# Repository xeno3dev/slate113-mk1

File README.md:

# Slate113 Mk1

## Overview

Slate113 Mk1 is a Beefy Phone-Like Cyberdeck, powered by the [ArmSOM CM5](https://www.armsom.org/product-page/cm5?variantId=052f14c0-9009-4c4c-8e45-79380a8dca78), and meant to be a more capable and feature-rich alternative to the Flipper One.

## Inspired By
[Pi Flux by Carbon Computers](https://carboncomputers.us/products/pi-flux) and the [Flipper One by Flipper Devices](https://blog.flipper.net/flipper-one-we-need-your-help/)

## Features
- DP Alt Mode
- ESP32 Co-Processor
- NFC via PN7160
- RFID via EM3095
- Sub-GHz via CC1101
- BadUSB
- Wi-Fi 6/6E and BLE 5.2
- 6 SMAs (Interchangable between GPS, WIFI, Sub-GHz, BLE, and LTE)
- SlateConnect (Custom Board-Edge Connector System)
- GNSS w/ IMU
- Cellular Modem (via M.2 B-Key Slot)
- Stereo Bottom Firing Speakers (w/ Amps)
- MEMS Microphone
- Side Mounted Customizable Adressable RGB LED Strip

## Sheets¹

### Main Board

Sheet BOM [here](./Manufacturing%20Files/BOMs/Per%20Sheet/slate113-mk1_main_board.csv)

---

### IO

Sheet BOM [here](./Manufacturing%20Files/BOMs/Per%20Sheet/slate113-mk1_io.csv)

---

### Power

Sheet BOM [here](./Manufacturing%20Files/BOMs/Per%20Sheet/slate113-mk1_power.csv)

---

### M.2

Sheet BOM [here](./Manufacturing%20Files/BOMs/Per%20Sheet/slate113-mk1_m.2.csv)

---

### Radio

Sheet BOM [here](./Manufacturing%20Files/BOMs/Per%20Sheet/slate113-mk1_radio.csv)

---

### Antenna Bracket

Sheet BOM [here](./Manufacturing%20Files/BOMs/Per%20Sheet/slate113-mk1_antennabracket.csv)

---

### SlateConnect

Sheet BOM [here](./Manufacturing%20Files/BOMs/Per%20Sheet/slate113-mk1_slateconnect.csv)

---

### LED Bar

Sheet BOM [here](./Manufacturing%20Files/BOMs/Per%20Sheet/slate113-mk1_ledbar.csv)

---

### PCB(s)²

Total BOM [here](./Manufacturing%20Files/BOMs/slate113-mk1.csv)

---

### Total Price Breakdown
---
| Item | Price | Link |
| --- | --- | --- |
| Main Board | USD$14.31 | [BOM](./Manufacturing%20Files/BOMs/Per%20Sheet/slate113-mk1_main_board.csv) |
| IO Board + Flex | USD$85.59 | [BOM](./Manufacturing%20Files/BOMs/Per%20Sheet/slate113-mk1_io.csv) |
| Power Board + Flex | USD$15.81 | [BOM](./Manufacturing%20Files/BOMs/Per%20Sheet/slate113-mk1_power.csv) |
| M.2 Board + Flex | USD$7.23 | [BOM](./Manufacturing%20Files/BOMs/Per%20Sheet/slate113-mk1_m.2.csv) |
| Radio Board + Flex | USD$77.90 | [BOM](./Manufacturing%20Files/BOMs/Per%20Sheet/slate113-mk1_radio.csv) |
| Antenna Bracket | USD$15.17 | [BOM](./Manufacturing%20Files/BOMs/Per%20Sheet/slate113-mk1_antennabracket.csv) |
| SlateConnect + Flex | USD$16.31 | [BOM](./Manufacturing%20Files/BOMs/Per%20Sheet/slate113-mk1_slateconnect.csv) |
| LED Bar Flex | USD$7.39 | [BOM](./Manufacturing%20Files/BOMs/Per%20Sheet/slate113-mk1_ledbar.csv) |
| Display | USD$55.49³ | [Alibaba Link](https://www.alibaba.com/product-detail/Industrial-5-5inch-Touch-Screen-720_1601790231031.html?spm=a2756.order-detail-ta-ta-b.0.0.fb3ef19cmzzMxB) |
| PCBs | ~USD$531⁴ | [JLCPCB](https://jlcpcb.com/) |

**Estimated Total**: US$971.53–1,286.53⁴

---

## Fineprint

¹Certain Sheets aren't included here, such as the Slate113 Sheet, as it's the root sheet, and has nothing, and the flex sheets (excluding the LED Bar Flex), as they are just two of the same connectors.

---

²Not Done at the time of writing this.

---

³Includes SHipping and DDP

---

⁴All parts haven't been finalized, including items like enclosure, battery, and others; subject to change

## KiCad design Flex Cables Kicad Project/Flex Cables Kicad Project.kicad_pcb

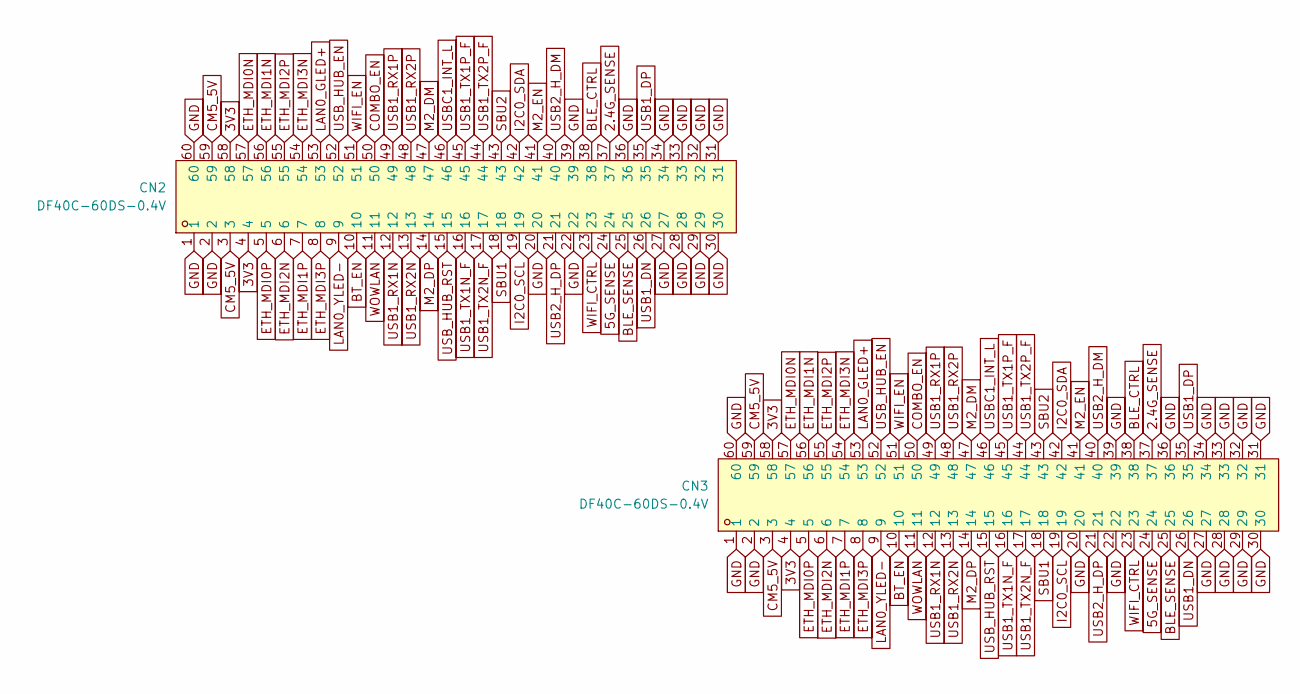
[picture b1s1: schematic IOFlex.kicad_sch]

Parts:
CN2, CN3: DF40C-60DS-0.4V; CONN-SMD_DF40C-60DS-0.4V-51; MPN DF40C-60DS-0.4V(51); LCSC Part C597938

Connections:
2.4G_SENSE: CN2.37, CN3.37
3V3: CN2.4, CN2.58, CN3.4, CN3.58; also elsewhere on the board
5G_SENSE: CN2.24, CN3.24
BLE_CTRL: CN2.38, CN3.38
BLE_SENSE: CN2.25, CN3.25
BT_EN: CN2.10, CN3.10
CM5_5V: CN2.3, CN2.59, CN3.3, CN3.59; also elsewhere on the board
COMBO_EN: CN2.50, CN3.50
ETH_MDI0N: CN2.57, CN3.57
ETH_MDI0P: CN2.5, CN3.5
ETH_MDI1N: CN2.56, CN3.56
ETH_MDI1P: CN2.7, CN3.7
ETH_MDI2N: CN2.6, CN3.6
ETH_MDI2P: CN2.55, CN3.55
ETH_MDI3N: CN2.54, CN3.54
ETH_MDI3P: CN2.8, CN3.8
GND: CN2.1, CN2.2, CN2.20, CN2.22, CN2.27, CN2.28, CN2.29, CN2.30, CN2.31, CN2.32, CN2.33, CN2.34, CN2.36, CN2.39, CN2.60, CN3.1, CN3.2, CN3.20, CN3.22, CN3.27, CN3.28, CN3.29, CN3.30, CN3.31, CN3.32, CN3.33, CN3.34, CN3.36, CN3.39, CN3.60; also elsewhere on the board
I2C0_SCL: CN2.19, CN3.19; also elsewhere on the board
I2C0_SDA: CN2.42, CN3.42; also elsewhere on the board
LAN0_GLED+: CN2.53, CN3.53
LAN0_YLED-: CN2.9, CN3.9
M2_DM: CN2.47, CN3.47; also elsewhere on the board
M2_DP: CN2.14, CN3.14; also elsewhere on the board
M2_EN: CN2.41, CN3.41
SBU1: CN2.18, CN3.18
SBU2: CN2.43, CN3.43
USB1_DN: CN2.26, CN3.26
USB1_DP: CN2.35, CN3.35
USB1_RX1N: CN2.12, CN3.12
USB1_RX1P: CN2.49, CN3.49
USB1_RX2N: CN2.13, CN3.13
USB1_RX2P: CN2.48, CN3.48
USB1_TX1N_F: CN2.16, CN3.16
USB1_TX1P_F: CN2.45, CN3.45
USB1_TX2N_F: CN2.17, CN3.17
USB1_TX2P_F: CN2.44, CN3.44
USB2_H_DM: CN2.40, CN3.40
USB2_H_DP: CN2.21, CN3.21
USBC1_INT_L: CN2.46, CN3.46
USB_HUB_EN: CN2.52, CN3.52
USB_HUB_RST: CN2.15, CN3.15
WIFI_CTRL: CN2.23, CN3.23
WIFI_EN: CN2.51, CN3.51
WOWLAN: CN2.11, CN3.11

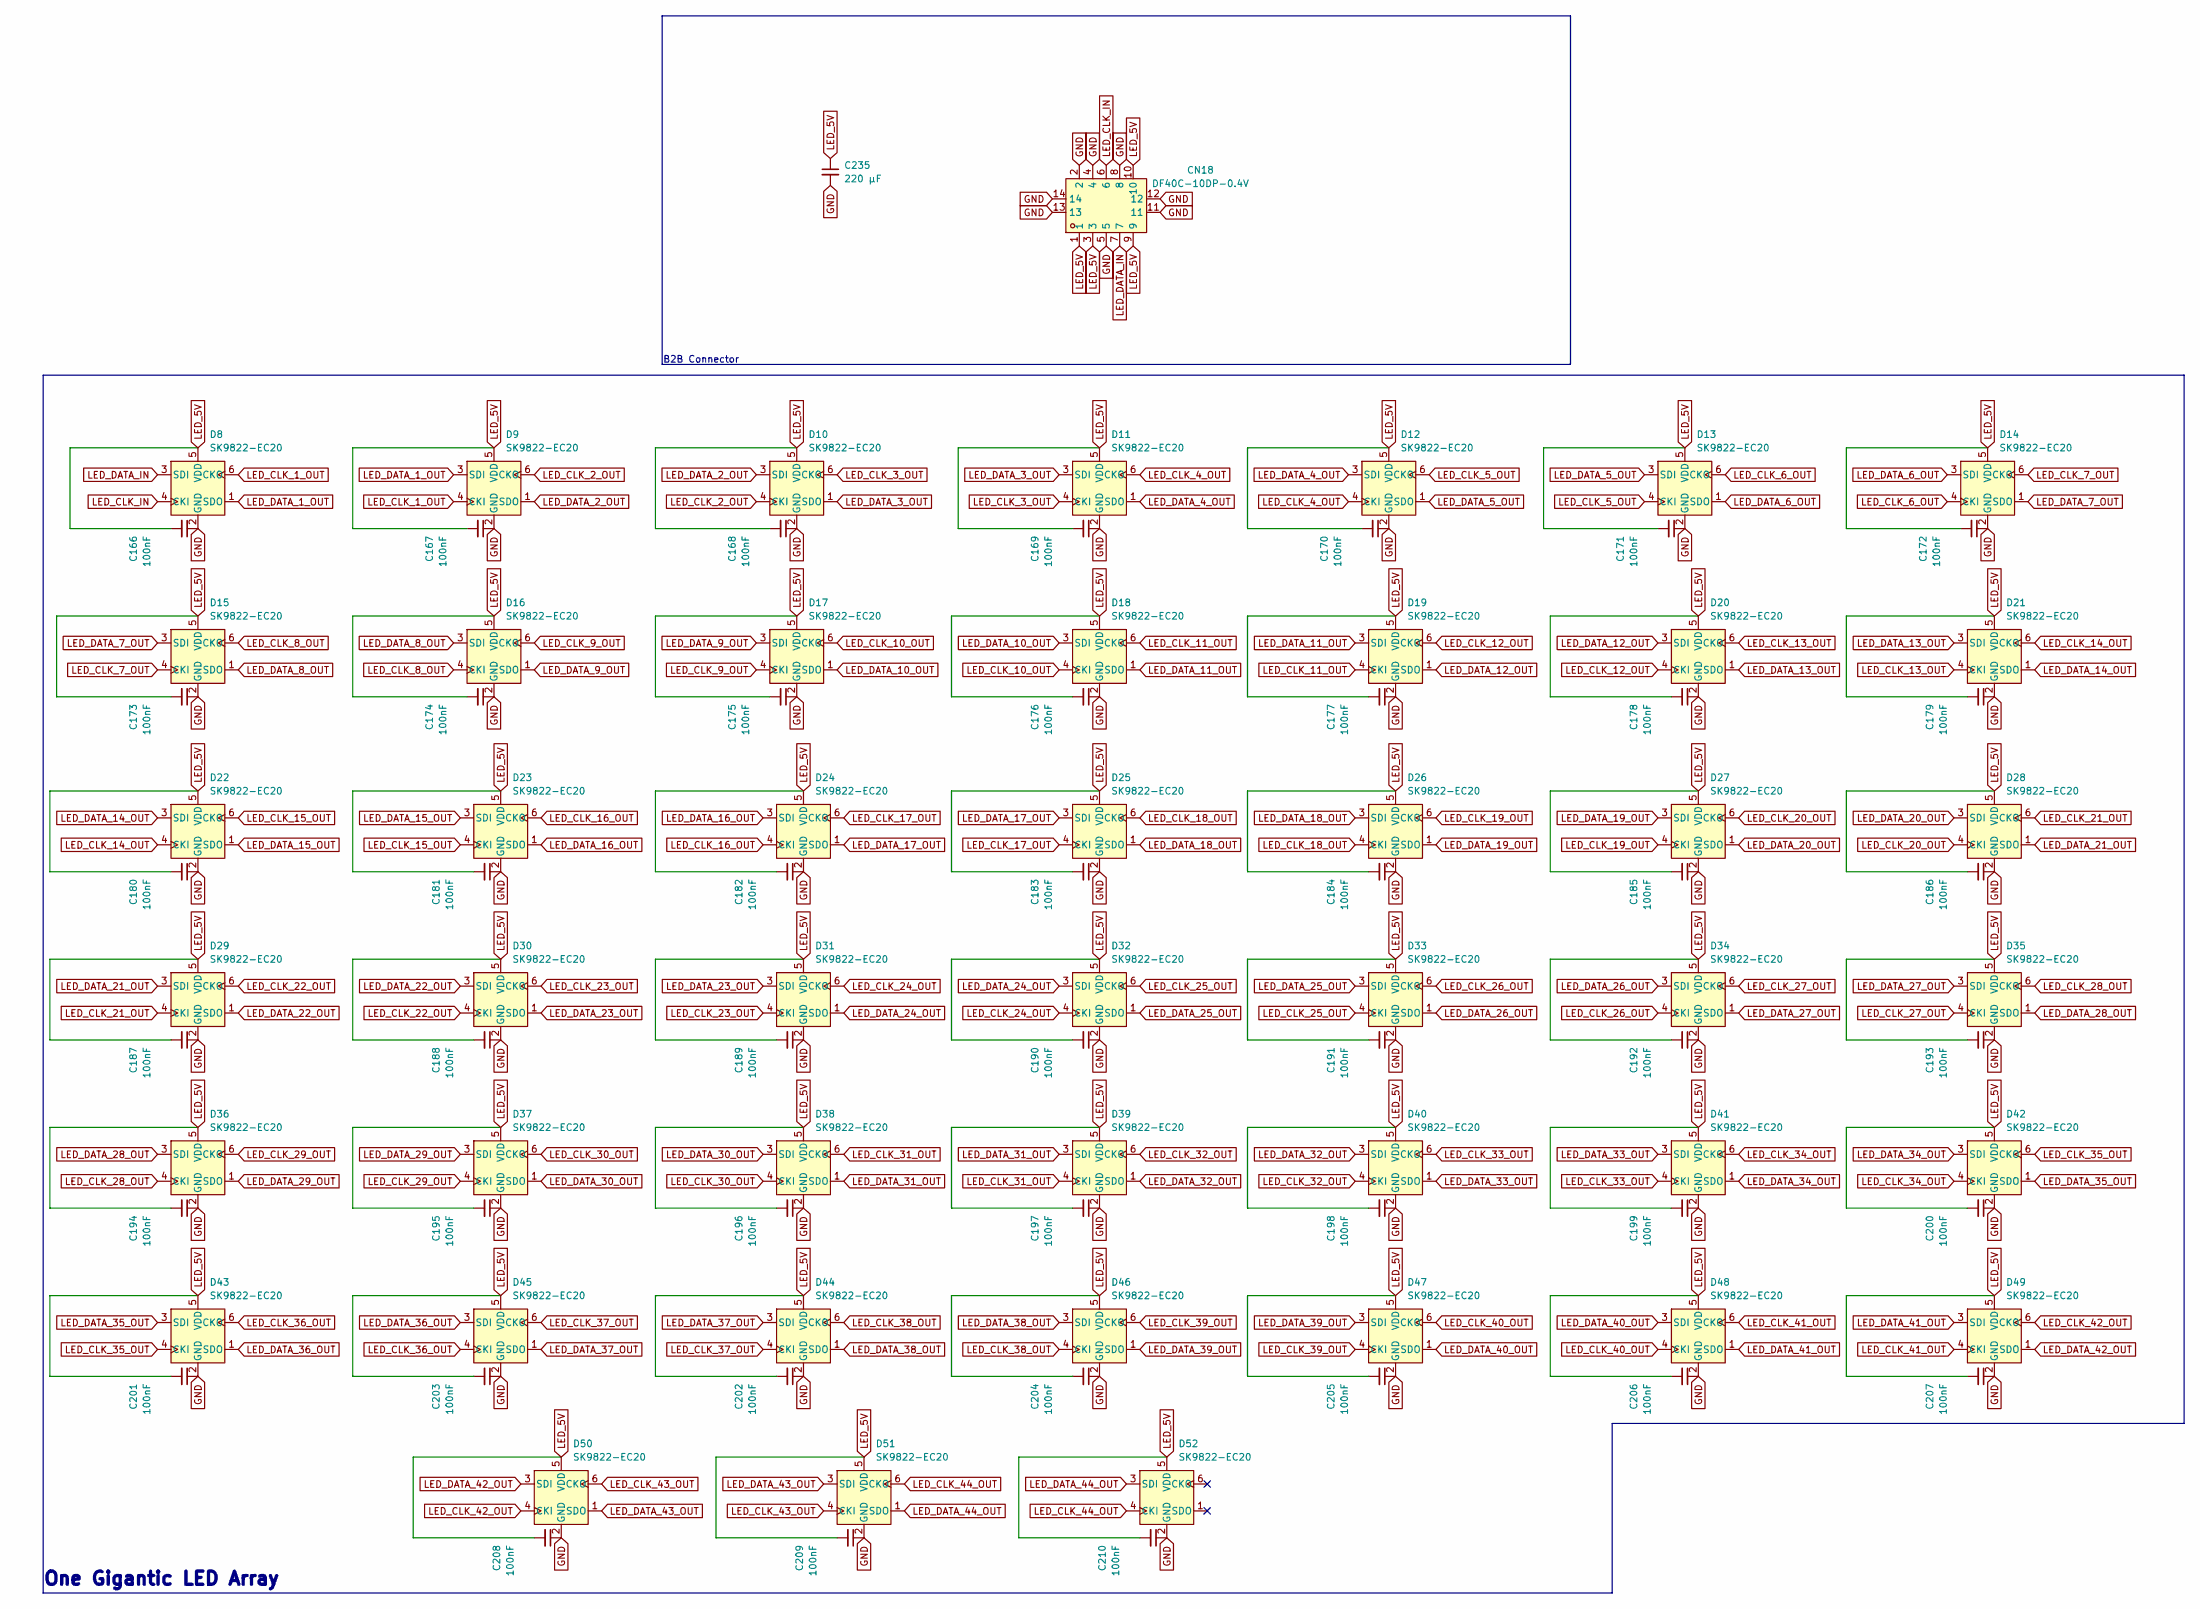
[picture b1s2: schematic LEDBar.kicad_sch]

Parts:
C166, C167, C168, C169, C170, C171, C172, C173, C174, C175, C176, C177, C178, C179, C180, C181, C182, C183, C184, C185, C186, C187, C188, C189, C190, C191, C192, C193, C194, C195, C196, C197, C198, C199, C200, C201, C202, C203, C204, C205, C206, C207, C208, C209, C210: 100nF; C_0603_1608Metric; MPN CL10B104KB8NNNC; LCSC Part C1591
C235: 220 µF; CHEMI-F61; MPN APXF6R3ARA221MF61G; DigiKey Part 565-3163-1-ND
CN18: DF40C-10DP-0.4V; CONN-SMD_10P-P0.40_DF40C-10DP-0.4V-51; MPN DF40C-10DP-0.4V(51); LCSC Part C424635
D8, D9, D10, D11, D12, D13, D14, D15, D16, D17, D18, D19, D20, D21, D22, D23, D24, D25, D26, D27, D28, D29, D30, D31, D32, D33, D34, D35, D36, D37, D38, D39, D40, D41, D42, D43, D44, D45, D46, D47, D48, D49, D50, D51, D52: SK9822-EC20; MPN SK9822-EC20; LCSC Part C2909059

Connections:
GND: C166.1, C167.1, C168.1, C169.1, C170.1, C171.1, C172.1, C173.1, C174.1, C175.1, C176.1, C177.1, C178.1, C179.1, C180.1, C181.1, C182.1, C183.1, C184.1, C185.1, C186.1, C187.1, C188.1, C189.1, C190.1, C191.1, C192.1, C193.1, C194.1, C195.1, C196.1, C197.1, C198.1, C199.1, C200.1, C201.1, C202.1, C203.1, C204.1, C205.1, C206.1, C207.1, C208.1, C209.1, C210.1, C235.2, CN18.2, CN18.4, CN18.5, CN18.8, CN18.11, CN18.12, CN18.13, CN18.14, D8.2 (GND), D9.2 (GND), D10.2 (GND), D11.2 (GND), D12.2 (GND), D13.2 (GND), D14.2 (GND), D15.2 (GND), D16.2 (GND), D17.2 (GND), D18.2 (GND), D19.2 (GND), D20.2 (GND), D21.2 (GND), D22.2 (GND), D23.2 (GND), D24.2 (GND), D25.2 (GND), D26.2 (GND), D27.2 (GND), D28.2 (GND), D29.2 (GND), D30.2 (GND), D31.2 (GND), D32.2 (GND), D33.2 (GND), D34.2 (GND), D35.2 (GND), D36.2 (GND), D37.2 (GND), D38.2 (GND), D39.2 (GND), D40.2 (GND), D41.2 (GND), D42.2 (GND), D43.2 (GND), D44.2 (GND), D45.2 (GND), D46.2 (GND), D47.2 (GND), D48.2 (GND), D49.2 (GND), D50.2 (GND), D51.2 (GND), D52.2 (GND); also elsewhere on the board
LED_5V: C166.2, C167.2, C168.2, C169.2, C170.2, C171.2, C172.2, C173.2, C174.2, C175.2, C176.2, C177.2, C178.2, C179.2, C180.2, C181.2, C182.2, C183.2, C184.2, C185.2, C186.2, C187.2, C188.2, C189.2, C190.2, C191.2, C192.2, C193.2, C194.2, C195.2, C196.2, C197.2, C198.2, C199.2, C200.2, C201.2, C202.2, C203.2, C204.2, C205.2, C206.2, C207.2, C208.2, C209.2, C210.2, C235.1, CN18.1, CN18.3, CN18.9, CN18.10, D8.5 (VDD), D9.5 (VDD), D10.5 (VDD), D11.5 (VDD), D12.5 (VDD), D13.5 (VDD), D14.5 (VDD), D15.5 (VDD), D16.5 (VDD), D17.5 (VDD), D18.5 (VDD), D19.5 (VDD), D20.5 (VDD), D21.5 (VDD), D22.5 (VDD), D23.5 (VDD), D24.5 (VDD), D25.5 (VDD), D26.5 (VDD), D27.5 (VDD), D28.5 (VDD), D29.5 (VDD), D30.5 (VDD), D31.5 (VDD), D32.5 (VDD), D33.5 (VDD), D34.5 (VDD), D35.5 (VDD), D36.5 (VDD), D37.5 (VDD), D38.5 (VDD), D39.5 (VDD), D40.5 (VDD), D41.5 (VDD), D42.5 (VDD), D43.5 (VDD), D44.5 (VDD), D45.5 (VDD), D46.5 (VDD), D47.5 (VDD), D48.5 (VDD), D49.5 (VDD), D50.5 (VDD), D51.5 (VDD), D52.5 (VDD)
LED_CLK_1_OUT: D8.6 (CKO), D9.4 (CKI)
LED_CLK_2_OUT: D9.6 (CKO), D10.4 (CKI)
LED_CLK_3_OUT: D10.6 (CKO), D11.4 (CKI)
LED_CLK_4_OUT: D11.6 (CKO), D12.4 (CKI)
LED_CLK_5_OUT: D12.6 (CKO), D13.4 (CKI)
LED_CLK_6_OUT: D13.6 (CKO), D14.4 (CKI)
LED_CLK_7_OUT: D14.6 (CKO), D15.4 (CKI)
LED_CLK_8_OUT: D15.6 (CKO), D16.4 (CKI)
LED_CLK_9_OUT: D16.6 (CKO), D17.4 (CKI)
LED_CLK_10_OUT: D17.6 (CKO), D18.4 (CKI)
LED_CLK_11_OUT: D18.6 (CKO), D19.4 (CKI)
LED_CLK_12_OUT: D19.6 (CKO), D20.4 (CKI)
LED_CLK_13_OUT: D20.6 (CKO), D21.4 (CKI)
LED_CLK_14_OUT: D21.6 (CKO), D22.4 (CKI)
LED_CLK_15_OUT: D22.6 (CKO), D23.4 (CKI)
LED_CLK_16_OUT: D23.6 (CKO), D24.4 (CKI)
LED_CLK_17_OUT: D24.6 (CKO), D25.4 (CKI)
LED_CLK_18_OUT: D25.6 (CKO), D26.4 (CKI)
LED_CLK_19_OUT: D26.6 (CKO), D27.4 (CKI)
LED_CLK_20_OUT: D27.6 (CKO), D28.4 (CKI)
LED_CLK_21_OUT: D28.6 (CKO), D29.4 (CKI)
LED_CLK_22_OUT: D29.6 (CKO), D30.4 (CKI)
LED_CLK_23_OUT: D30.6 (CKO), D31.4 (CKI)
LED_CLK_24_OUT: D31.6 (CKO), D32.4 (CKI)
LED_CLK_25_OUT: D32.6 (CKO), D33.4 (CKI)
LED_CLK_26_OUT: D33.6 (CKO), D34.4 (CKI)
LED_CLK_27_OUT: D34.6 (CKO), D35.4 (CKI)
LED_CLK_28_OUT: D35.6 (CKO), D36.4 (CKI)
LED_CLK_29_OUT: D36.6 (CKO), D37.4 (CKI)
LED_CLK_30_OUT: D37.6 (CKO), D38.4 (CKI)
LED_CLK_31_OUT: D38.6 (CKO), D39.4 (CKI)
LED_CLK_32_OUT: D39.6 (CKO), D40.4 (CKI)
LED_CLK_33_OUT: D40.6 (CKO), D41.4 (CKI)
LED_CLK_34_OUT: D41.6 (CKO), D42.4 (CKI)
LED_CLK_35_OUT: D42.6 (CKO), D43.4 (CKI)
LED_CLK_36_OUT: D43.6 (CKO), D45.4 (CKI)
LED_CLK_37_OUT: D44.4 (CKI), D45.6 (CKO)
LED_CLK_38_OUT: D44.6 (CKO), D46.4 (CKI)
LED_CLK_39_OUT: D46.6 (CKO), D47.4 (CKI)
LED_CLK_40_OUT: D47.6 (CKO), D48.4 (CKI)
LED_CLK_41_OUT: D48.6 (CKO), D49.4 (CKI)
LED_CLK_42_OUT: D49.6 (CKO), D50.4 (CKI)
LED_CLK_43_OUT: D50.6 (CKO), D51.4 (CKI)
LED_CLK_44_OUT: D51.6 (CKO), D52.4 (CKI)
LED_CLK_IN: CN18.6, D8.4 (CKI)
LED_DATA_1_OUT: D8.1 (SDO), D9.3 (SDI)
LED_DATA_2_OUT: D9.1 (SDO), D10.3 (SDI)
LED_DATA_3_OUT: D10.1 (SDO), D11.3 (SDI)
LED_DATA_4_OUT: D11.1 (SDO), D12.3 (SDI)
LED_DATA_5_OUT: D12.1 (SDO), D13.3 (SDI)
LED_DATA_6_OUT: D13.1 (SDO), D14.3 (SDI)
LED_DATA_7_OUT: D14.1 (SDO), D15.3 (SDI)
LED_DATA_8_OUT: D15.1 (SDO), D16.3 (SDI)
LED_DATA_9_OUT: D16.1 (SDO), D17.3 (SDI)
LED_DATA_10_OUT: D17.1 (SDO), D18.3 (SDI)
LED_DATA_11_OUT: D18.1 (SDO), D19.3 (SDI)
LED_DATA_12_OUT: D19.1 (SDO), D20.3 (SDI)
LED_DATA_13_OUT: D20.1 (SDO), D21.3 (SDI)
LED_DATA_14_OUT: D21.1 (SDO), D22.3 (SDI)
LED_DATA_15_OUT: D22.1 (SDO), D23.3 (SDI)
LED_DATA_16_OUT: D23.1 (SDO), D24.3 (SDI)
LED_DATA_17_OUT: D24.1 (SDO), D25.3 (SDI)
LED_DATA_18_OUT: D25.1 (SDO), D26.3 (SDI)
LED_DATA_19_OUT: D26.1 (SDO), D27.3 (SDI)
LED_DATA_20_OUT: D27.1 (SDO), D28.3 (SDI)
LED_DATA_21_OUT: D28.1 (SDO), D29.3 (SDI)
LED_DATA_22_OUT: D29.1 (SDO), D30.3 (SDI)
LED_DATA_23_OUT: D30.1 (SDO), D31.3 (SDI)
LED_DATA_24_OUT: D31.1 (SDO), D32.3 (SDI)
LED_DATA_25_OUT: D32.1 (SDO), D33.3 (SDI)
LED_DATA_26_OUT: D33.1 (SDO), D34.3 (SDI)
LED_DATA_27_OUT: D34.1 (SDO), D35.3 (SDI)
LED_DATA_28_OUT: D35.1 (SDO), D36.3 (SDI)
LED_DATA_29_OUT: D36.1 (SDO), D37.3 (SDI)
LED_DATA_30_OUT: D37.1 (SDO), D38.3 (SDI)
LED_DATA_31_OUT: D38.1 (SDO), D39.3 (SDI)
LED_DATA_32_OUT: D39.1 (SDO), D40.3 (SDI)
LED_DATA_33_OUT: D40.1 (SDO), D41.3 (SDI)
LED_DATA_34_OUT: D41.1 (SDO), D42.3 (SDI)
LED_DATA_35_OUT: D42.1 (SDO), D43.3 (SDI)
LED_DATA_36_OUT: D43.1 (SDO), D45.3 (SDI)
LED_DATA_37_OUT: D44.3 (SDI), D45.1 (SDO)
LED_DATA_38_OUT: D44.1 (SDO), D46.3 (SDI)
LED_DATA_39_OUT: D46.1 (SDO), D47.3 (SDI)
LED_DATA_40_OUT: D47.1 (SDO), D48.3 (SDI)
LED_DATA_41_OUT: D48.1 (SDO), D49.3 (SDI)
LED_DATA_42_OUT: D49.1 (SDO), D50.3 (SDI)
LED_DATA_43_OUT: D50.1 (SDO), D51.3 (SDI)
LED_DATA_44_OUT: D51.1 (SDO), D52.3 (SDI)
LED_DATA_IN: CN18.7, D8.3 (SDI)

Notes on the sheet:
B2B Connector
One Gigantic LED Array

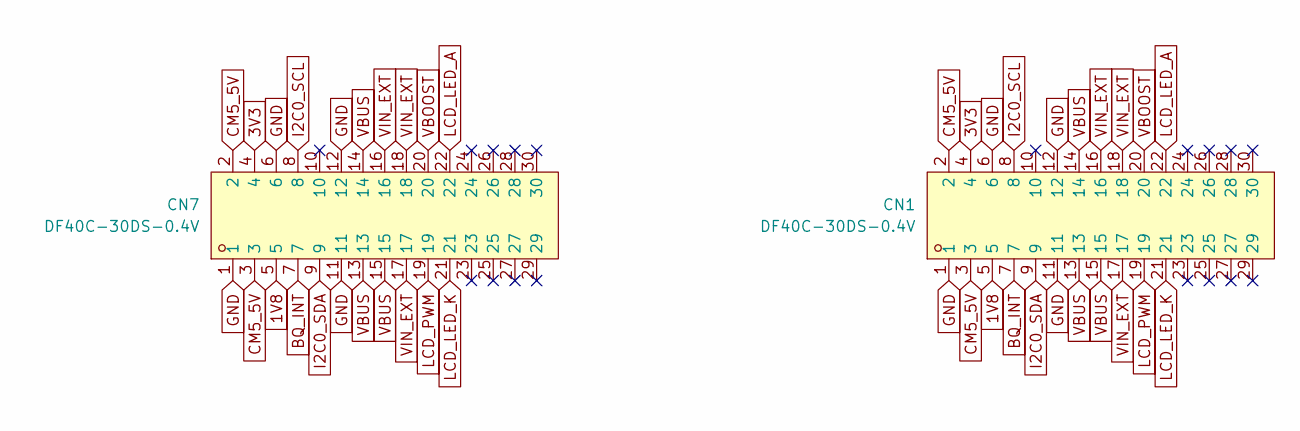
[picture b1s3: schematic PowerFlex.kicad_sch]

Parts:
CN1, CN7: DF40C-30DS-0.4V; CONN-SMD_DF40C-30DS-0.4V51; MPN DF40C-30DS-0.4V(51); LCSC Part C424642

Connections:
1V8: CN1.5, CN7.5; also elsewhere on the board
3V3: CN1.4, CN7.4; also elsewhere on the board
BQ_INT: CN1.7, CN7.7
CM5_5V: CN1.2, CN1.3, CN7.2, CN7.3; also elsewhere on the board
GND: CN1.1, CN1.6, CN1.11, CN1.12, CN7.1, CN7.6, CN7.11, CN7.12; also elsewhere on the board
I2C0_SCL: CN1.8, CN7.8; also elsewhere on the board
I2C0_SDA: CN1.9, CN7.9; also elsewhere on the board
LCD_LED_A: CN1.22, CN7.22
LCD_LED_K: CN1.21, CN7.21
LCD_PWM: CN1.19, CN7.19
VBOOST: CN1.20, CN7.20
VBUS: CN1.13, CN1.14, CN1.15, CN7.13, CN7.14, CN7.15; also elsewhere on the board
VIN_EXT: CN1.16, CN1.17, CN1.18, CN7.16, CN7.17, CN7.18; also elsewhere on the board

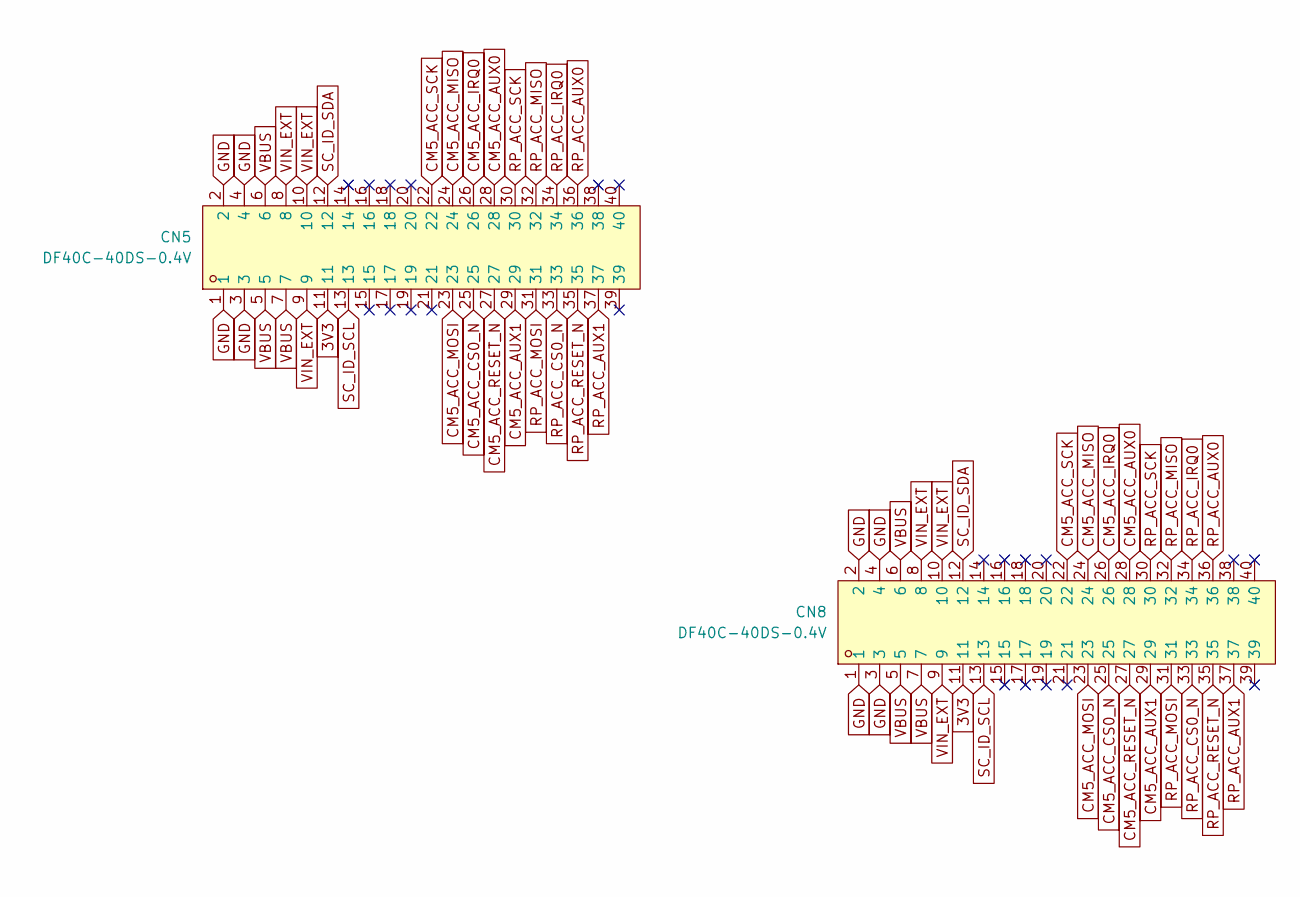
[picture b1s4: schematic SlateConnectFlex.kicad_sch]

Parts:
CN5, CN8: DF40C-40DS-0.4V; CONN-SMD_DF40C-40DS-0.4V51; MPN DF40C-40DS-0.4V(51); LCSC Part C424644

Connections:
3V3: CN5.11, CN8.11; also elsewhere on the board
CM5_ACC_AUX0: CN5.28, CN8.28
CM5_ACC_AUX1: CN5.29, CN8.29
CM5_ACC_CS0_N: CN5.25, CN8.25
CM5_ACC_IRQ0: CN5.26, CN8.26
CM5_ACC_MISO: CN5.24, CN8.24
CM5_ACC_MOSI: CN5.23, CN8.23
CM5_ACC_RESET_N: CN5.27, CN8.27
CM5_ACC_SCK: CN5.22, CN8.22
GND: CN5.1, CN5.2, CN5.3, CN5.4, CN8.1, CN8.2, CN8.3, CN8.4; also elsewhere on the board
RP_ACC_AUX0: CN5.36, CN8.36; also elsewhere on the board
RP_ACC_AUX1: CN5.37, CN8.37; also elsewhere on the board
RP_ACC_CS0_N: CN5.33, CN8.33; also elsewhere on the board
RP_ACC_IRQ0: CN5.34, CN8.34; also elsewhere on the board
RP_ACC_MISO: CN5.32, CN8.32; also elsewhere on the board
RP_ACC_MOSI: CN5.31, CN8.31; also elsewhere on the board
RP_ACC_RESET_N: CN5.35, CN8.35; also elsewhere on the board
RP_ACC_SCK: CN5.30, CN8.30; also elsewhere on the board
SC_ID_SCL: CN5.13, CN8.13
SC_ID_SDA: CN5.12, CN8.12
VBUS: CN5.5, CN5.6, CN5.7, CN8.5, CN8.6, CN8.7; also elsewhere on the board
VIN_EXT: CN5.8, CN5.9, CN5.10, CN8.8, CN8.9, CN8.10; also elsewhere on the board

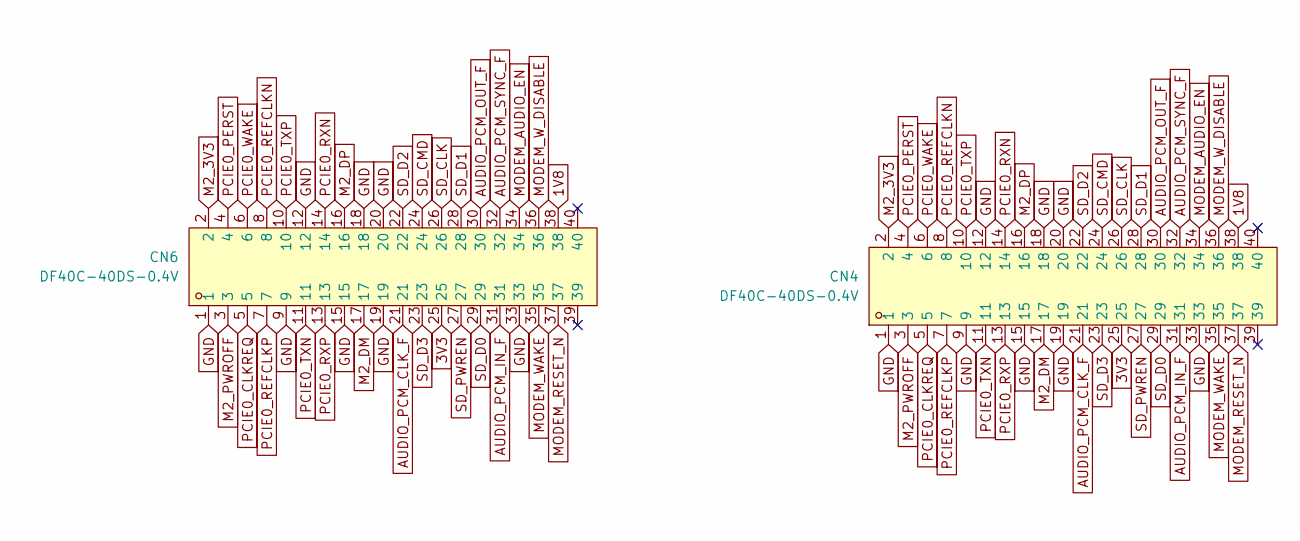
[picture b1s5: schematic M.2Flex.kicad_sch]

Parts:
CN4, CN6: DF40C-40DS-0.4V; CONN-SMD_DF40C-40DS-0.4V51; MPN DF40C-40DS-0.4V(51); LCSC Part C424644

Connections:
1V8: CN4.38, CN6.38; also elsewhere on the board
3V3: CN4.25, CN6.25; also elsewhere on the board
AUDIO_PCM_CLK_F: CN4.21, CN6.21
AUDIO_PCM_IN_F: CN4.31, CN6.31
AUDIO_PCM_OUT_F: CN4.30, CN6.30
AUDIO_PCM_SYNC_F: CN4.32, CN6.32
GND: CN4.1, CN4.9, CN4.12, CN4.15, CN4.18, CN4.19, CN4.20, CN4.33, CN6.1, CN6.9, CN6.12, CN6.15, CN6.18, CN6.19, CN6.20, CN6.33; also elsewhere on the board
M2_3V3: CN4.2, CN6.2
M2_DM: CN4.17, CN6.17; also elsewhere on the board
M2_DP: CN4.16, CN6.16; also elsewhere on the board
M2_PWROFF: CN4.3, CN6.3
MODEM_AUDIO_EN: CN4.34, CN6.34
MODEM_RESET_N: CN4.37, CN6.37
MODEM_WAKE: CN4.35, CN6.35
MODEM_W_DISABLE: CN4.36, CN6.36
PCIE0_CLKREQ: CN4.5, CN6.5
PCIE0_PERST: CN4.4, CN6.4
PCIE0_REFCLKN: CN4.8, CN6.8
PCIE0_REFCLKP: CN4.7, CN6.7
PCIE0_RXN: CN4.14, CN6.14
PCIE0_RXP: CN4.13, CN6.13
PCIE0_TXN: CN4.11, CN6.11
PCIE0_TXP: CN4.10, CN6.10
PCIE0_WAKE: CN4.6, CN6.6
SD_CLK: CN4.26, CN6.26
SD_CMD: CN4.24, CN6.24
SD_D0: CN4.29, CN6.29
SD_D1: CN4.28, CN6.28
SD_D2: CN4.22, CN6.22
SD_D3: CN4.23, CN6.23
SD_PWREN: CN4.27, CN6.27

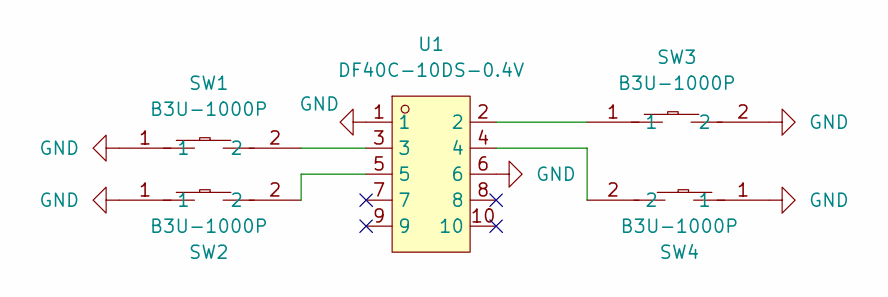
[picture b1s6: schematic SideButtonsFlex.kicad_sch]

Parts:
SW1, SW2, SW3, SW4: B3U-1000P; KEY-SMD_B3U-1000PM; MPN B3U-1000P; LCSC Part C231329
U1: DF40C-10DS-0.4V; CONN-SMD_10P-P0.40_HRS_DF40C-10DS-0.4V-51; MPN DF40C-10DS-0.4V(51); LCSC Part C424636

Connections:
GND: SW1.1, SW2.1, SW3.2, SW4.1, U1.1, U1.6; also elsewhere on the board
unnamed: SW1.2, U1.3
unnamed: SW2.2, U1.5
unnamed: SW3.1, U1.2
unnamed: SW4.2, U1.4

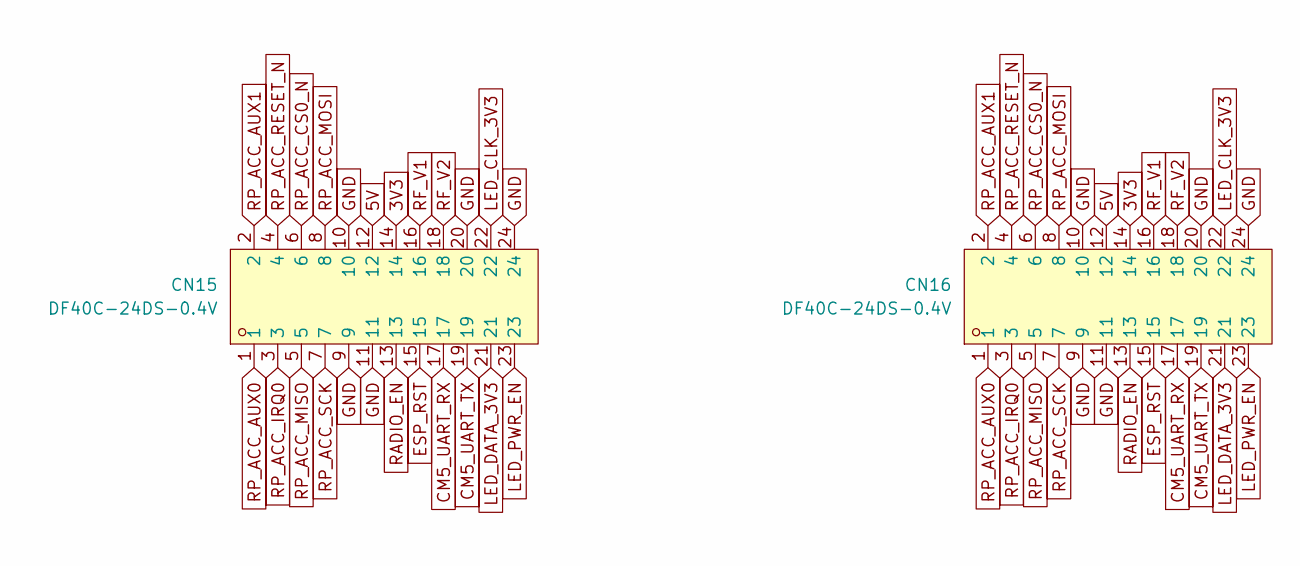
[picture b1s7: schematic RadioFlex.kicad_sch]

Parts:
CN15, CN16: DF40C-24DS-0.4V; CONN-SMD_DF40C-24DS-0.4V51; MPN DF40C-24DS-0.4V(51); LCSC Part C424640

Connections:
3V3: CN15.14, CN16.14; also elsewhere on the board
5V: CN15.12, CN16.12
CM5_UART_RX: CN15.17, CN16.17
CM5_UART_TX: CN15.19, CN16.19
ESP_RST: CN15.15, CN16.15
GND: CN15.9, CN15.10, CN15.11, CN15.20, CN15.24, CN16.9, CN16.10, CN16.11, CN16.20, CN16.24; also elsewhere on the board
LED_CLK_3V3: CN15.22, CN16.22
LED_DATA_3V3: CN15.21, CN16.21
LED_PWR_EN: CN15.23, CN16.23
RADIO_EN: CN15.13, CN16.13
RF_V1: CN15.16, CN16.16
RF_V2: CN15.18, CN16.18
RP_ACC_AUX0: CN15.1, CN16.1; also elsewhere on the board
RP_ACC_AUX1: CN15.2, CN16.2; also elsewhere on the board
RP_ACC_CS0_N: CN15.6, CN16.6; also elsewhere on the board
RP_ACC_IRQ0: CN15.3, CN16.3; also elsewhere on the board
RP_ACC_MISO: CN15.5, CN16.5; also elsewhere on the board
RP_ACC_MOSI: CN15.8, CN16.8; also elsewhere on the board
RP_ACC_RESET_N: CN15.4, CN16.4; also elsewhere on the board
RP_ACC_SCK: CN15.7, CN16.7; also elsewhere on the board

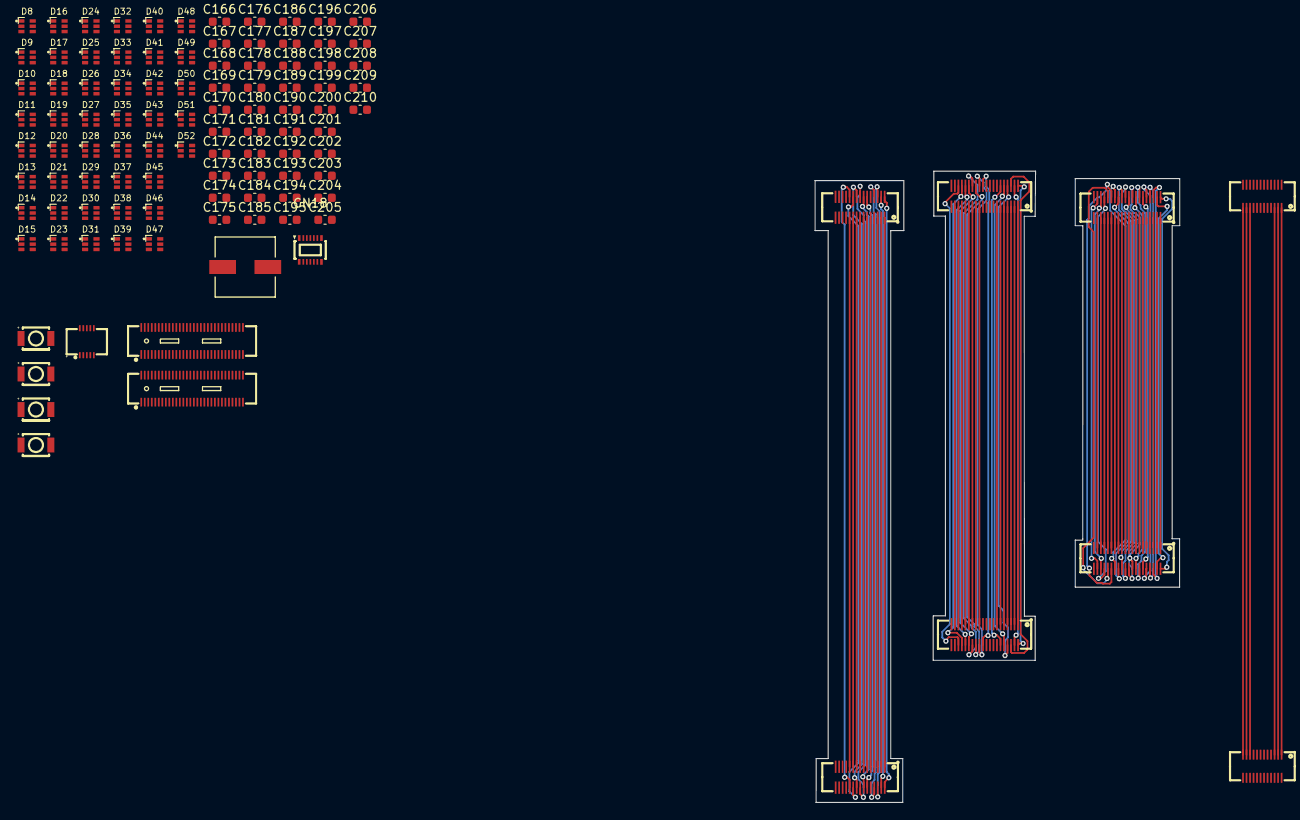
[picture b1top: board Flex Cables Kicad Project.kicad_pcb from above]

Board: 2 copper layers, 41.6 x 72.0 mm, 107 parts (0 on the bottom side), 201 nets.

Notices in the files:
README.md:
License: CC BY-NC-SA 4.0
